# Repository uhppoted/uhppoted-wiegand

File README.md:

# uhppoted-wiegand

`uhppoted-wiegand` implements a RaspberryPi RP2040 based reader/emulator for a Wiegand-26 interface for:
- development, testing and debugging of access control software
- interfacing non-standard and off-brand readers and keypads to the UHPPOTE L0x access controllers

The project includes:
- _M5Stack_ Wiegand-26 emulator with:
   - isolated interface capable driving up to 32mA loads
   - can be powered from M5 bus, USB or external 12VDC supply
   - emulates both card reader and 4-bit/8-bit keypad modes
   - can operate either standalone or as an _M5Stack_ module

- breadboard prototypes
   - PIO based Wiegand-26 reader emulator which can write a Wiegand-26 card out to a controller
   - PIO based Wiegand-26 controller emulator which can read from Wiegand-26 reader and unlock a door
   - PIO based Wiegand-26 'universal' reader/writer implementation

## Status

### M5Stack

1. Wiegand emulator (Rev. 0)

|||

Includes:
- KiCad schematic and PCB layout
- Firmware for _Waveshare Tiny RP2040_
- Example Micropython application for _M5Stack_ _CoreS3_.

#### Errata
1. Pads for SK6812 are incorrectly numbered.
2. Anode and cathode swapped pads for D2, D3 and D4 are swapped.
3. ISO7841 doesn't allow RC filter on LED input.
4. Insufficient clearance around mounting holes.
5. DI and DO are pulled low on power-up (should default to _high_).
6. Solder mask does not include M5 connectors.
7. GPIO pins are incorrect (IO1 and IO2 instead of IO6 and IO7).

### Prototype

Breadboarded and Fritzing'ed implementations of:
- Wiegand-26 reader emulator
- Wiegand-26 controller emulator
- Wiegand-26 'universal' reader/writer

## Release Notes

### Current Release

## [0.9.1](https://codeberg.org/uhppoted/uhppoted-wiegand/releases/tag/v0.9.1) - 2026-10-13

1. Migrated from _github._ to _codeberg_.
2. Updated to Go 1.27.
3. Updated to pico-sdk_2.3.1.

## Breadboard

### Building from source

Required tools:
- [Raspberry Pi Pico C/C++ SDK](https://datasheets.raspberrypi.com/pico/raspberry-pi-pico-c-sdk.pdf)
- Compatible C/C++ compiler
- _make_
- [PicoProbe](https://github.com/raspberrypi/picoprobe) (optional but recommended)
- [OpenOCD](https://github.com/raspberrypi/openocd.git) (optional but recommended)
- [PicoTool](https://github.com/raspberrypi/picotool) (optional but recommended)

To build using the included _Makefile_:
```
git clone https://codeberg.org/uhppoted/uhppoted-wiegand.git
cd uhppoted-wiegand/breadboard/pico
make clean
make build
```

The `build` target produces both a UF2 and an ELF binary for installation on a _Raspberry Pi Pico_ using either:
- USB (using _BOOTSEL_)
- _PicoProbe_ + _OpenOCD_
- _PicoTool_

- The `make install` command installs the binary using _PicoTool_
- The `make run` command installs the binary using _PicoProbe_ and _OpenOCD_

### Usage

The provided software includes a **very** bare bones serial port command interface. Commands are (currently)
single letter mnemonics and need to be terminated by a carriage return and/or line feed.

The supported command set comprises:

| *Command*                | *Mode*       | *Description*                             |
| -------------------------|--------------|-------------------------------------------|
| TIME yyyy-mm-dd HH:mm:ss | _ALL_        | Set date/time                             |
| CARD nnnnnnnn            | _emulator_   | Emulates card swipe                       |
| CODE dddddd              | _emulator_   | Emulates keypad                           |
|                          |              |                                           |
| LIST ACL                 | _controller_ | List cards in ACL                         |
| CLEAR ACL                | _controller_ | Deletes all cards in ACL                  |
| GRANT nnnnnn dddddd      | _controller_ | Grant card (+ optional PIN) access rights |
| REVOKE nnnnnn            | _controller_ | Revoke card access rights                 |
| QUERY                    | _controller_ | Display last card read/write              |
|                          |              |                                           |
| MOUNT                    | _ALL_        | Mount SD card                             |
| UNMOUNT                  | _ALL_        | Unmount SD card                           |
| FORMAT                   | _ALL_        | Format SD card                            |
|                          |              |                                           |
| UNLOCK                   | _controller_ | Unlocks door for 5 seconds                |
|                          |              |                                           |
| OPEN                     | _emulator_   | Emulates door open contact                |
| CLOSE                    | _emulator_   | Emulates door close contact               |
| PRESS                    | _emulator_   | Emulates pushbutton press                 |
| RELEASE                  | _emulator_   | Emulates pushbutton release               |
|                          |              |                                           |
| BLINK                    | _ALL_        | Blinks reader LED 5 times                 |
| CLS                      | _ALL_        | Reinitialises terminal                    |
| REBOOT                   | _ALL_        | Reboot                                    |
| ?                        | _ALL_        | Display list of commands                  |

### Operating Modes

The codebase currently supports two operating modes:
- emulator
- controller

In _emulator_ mode the implementation writes a Wiegand-26 card code (or keypad PIN code) to an external Wiegand-26 interface
(e.g. a UHPPOTE controller). It also:
- emulates a door open/closed sensor
- emulates a door pushbutton
- detects the door locked/unlocked state

In _controller_ mode the implementation reads a Wiegand-26 card code (or keypad PIN code) from an external Wiegand-26 reader/keypad. It also:
- detects a door open/closed sensor state change
- detects a door pushbutton state change
- emulates a door lock/unlock
- implements card permissions and keypad passcodes

The operating mode is set by the combination of the code and the JUMPER_READ and JUMPER_WRITE inputs (set in _hwconfig.c_, 
GPIO7 and GPIO8 by default):
- the _controller_ binaries expect the JUMPER_READ input to be pulled LOW
- the _emulator_ binaries expected the JUMPER_WRITE input to be pulled LOW
- the _universal_ binaries start in _reader_ mode if the JUMPER_READ input is pulled LOW, or in _writer_ mode if the 
  JUMPER_WRITE is pulled LOW
- if both JUMPER_READ and JUMPER_WRITE are pulled LOW the operating mode is UNKNOWN.

### Keypad emulation

The code supports two keypad modes:
- 4-bit burst mode
- 8-bit burst mode

In 4 bit burst mode, each keypress is sent as 4 bit code followed by a 28-bit 'space', with keypad digits encoded as follows:

| Digit | 0    | 1    | 2    | 3    | 4    | 5    | 6    | 7    | 8    | 9    | *    | #    |
|-------|------|------|------|------|------|------|------|------|------|------|------|------|
| Code  | 0000 | 0001 | 0010 | 0011 | 0100 | 0101 | 0110 | 0111 | 1000 | 1001 | 1010 | 1011 |

In 8 bit burst mode, each keypress is sent as 8 bit code followed by a 24-bit 'space', with keypad digits encoded as follows:

| Digit | 0        | 1        | 2        | 3        | 4        | 5        | 6        | 7        | 8        | 9        | *        | #        |
|-------|----------|----------|----------|----------|----------|----------|----------|----------|----------|----------|----------|----------|
| Code  | 11110000 | 11100001 | 11010010 | 11000011 | 10110100 | 10100101 | 10010110 | 10000111 | 01111000 | 01101001 | 01011010 | 01001011 |

- In _emulator_ operating mode, the keypad mode is set by the `KEYPAD` build constant ('4-bit' or '8-bit')
- In _controller_ operating mode the keypad reader can detect and read both keypad encodings. A keycode is terminated by either a
  '#' or a 12.5 second timeout.

### Supervisor passcodes

The supervisor passcodes are _controller_ operating mode override codes that unconditionally unlocks the door.

The _controller_ operating mode supports up to four user-defined passcodes which can be set (or cleared) using the 
_PASSCODES_ command in the CLI. The passcodes may be up to 6 digits in length.

### Master passcode

In addition to the supervisor passcodes, the _controller_ operating mode provides for a MASTER override code that
unconditionally unlocks the door. The _MASTER_ override code is set at build time via the `MASTER_PASSCODE` build constant.

### Build constants

The _build constants_ in the _Makefiles_ define the initial operational settings:

| *Constant*           | *Description*                                                                                             |
|----------------------|-----------------------------------------------------------------------------------------------------------|
| `FACILITY_CODE`      | The default facility code for _emulator_ mode, used if the _CARD_ command card number is 5 digits or less |
| `SYSDATE`            | Initial system date                                                                                       |
| `SYSTIME`            | Initial system time                                                                                       |
| `MASTER_PASSCODE`    | Default master access override code                                                                       |
| `KEYPAD`             | Keypad mode ('4-bit' or '8-bit')                                                                          |
| `SSID`               | WiFi SSID                                                                                                 |
| `PASSWORD`           | WiFi password                                                                                             |
| `TCPD_CLI_PORT`      | TCP port for the Telnet CLI                                                                               |
| `TCPD_LOG_PORT`      | TCP port for the network logger                                                                           |
| `TCPD_SERVER_IDLE`   | Idle time (seconds) after which the TCP server closes all connections and restarts                        |
| `TCPD_CLIENT_IDLE`   | Idle time (seconds) after which a Telnet CLI client connection is closed                                  |
| `TCPD_POLL_INTERVAL` | Internal TCP handler poll interval (ms)                                                                   |
## License

Hardware is licensed under the CERN-OHL-S-2.0-S license, software is licensed under the MIT license.

## References and Related Projects

1. [Getting started with the Raspberry Pi Pico](https://datasheets.raspberrypi.com/pico/getting-started-with-pico.pdf)

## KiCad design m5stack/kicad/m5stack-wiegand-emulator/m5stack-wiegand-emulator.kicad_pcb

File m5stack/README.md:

# M5Stack Wiegand Emulator

RP2040 _M5Stack_ module to emulate a Wiegand reader:

- Emulates a single Wiegand-26 card reader/keypad with an LED. 
- Implements the M5Stack serial interface.
- Intended for use with an M5 _base_ module but can optionally be powered via the external connector
  for standalone use.

## Raison d'être

Mostly to avoid having to dig out a breadboard and figure how it worked all over again every time I needed
to test a Wiegand interface.

## Notes

1. The emulator uses a line driver to interface to the external controller i.e. it is not an open-collector
   and cannot be "parallelised" (as in e.g. [Will this circuit for two Wiegand card readers allow them to talk to one control board?](https://electronics.stackexchange.com/questions/535159/will-this-circuit-for-two-wiegand-card-readers-allow-them-to-talk-to-one-control). Which TBH is kindof a weird thing to do but ..).

## Status

**IN DEVELOPMENT**

## Design Notes

### Rev.0

1. The RP2040 is **way** overkill for this application but makes for a nice development setup.
2. It's more logicial to have the ISO784x on the other side of the RP2040 but for now it allows for powering via
   USB during development.

#### Errata
1. Pads for WS2812/SK6812 are incorrectly numbered.
2. Pads for D2, D3 and D4 are incorrect (anode and cathode swapped).
3. ISO7841 doesn't allow RC filter on LED input.

## References

1. [M5Stack](https://m5stack.com)
2. [WaveShare RP2040-Tiny](https://www.waveshare.com/wiki/RP2040-Tiny)
3. [M5 Core Schematic(20171206)](https://m5stack.oss-cn-shenzhen.aliyuncs.com/resource/docs/schematic/Core/M5-Core-Schematic(20171206).pdf)

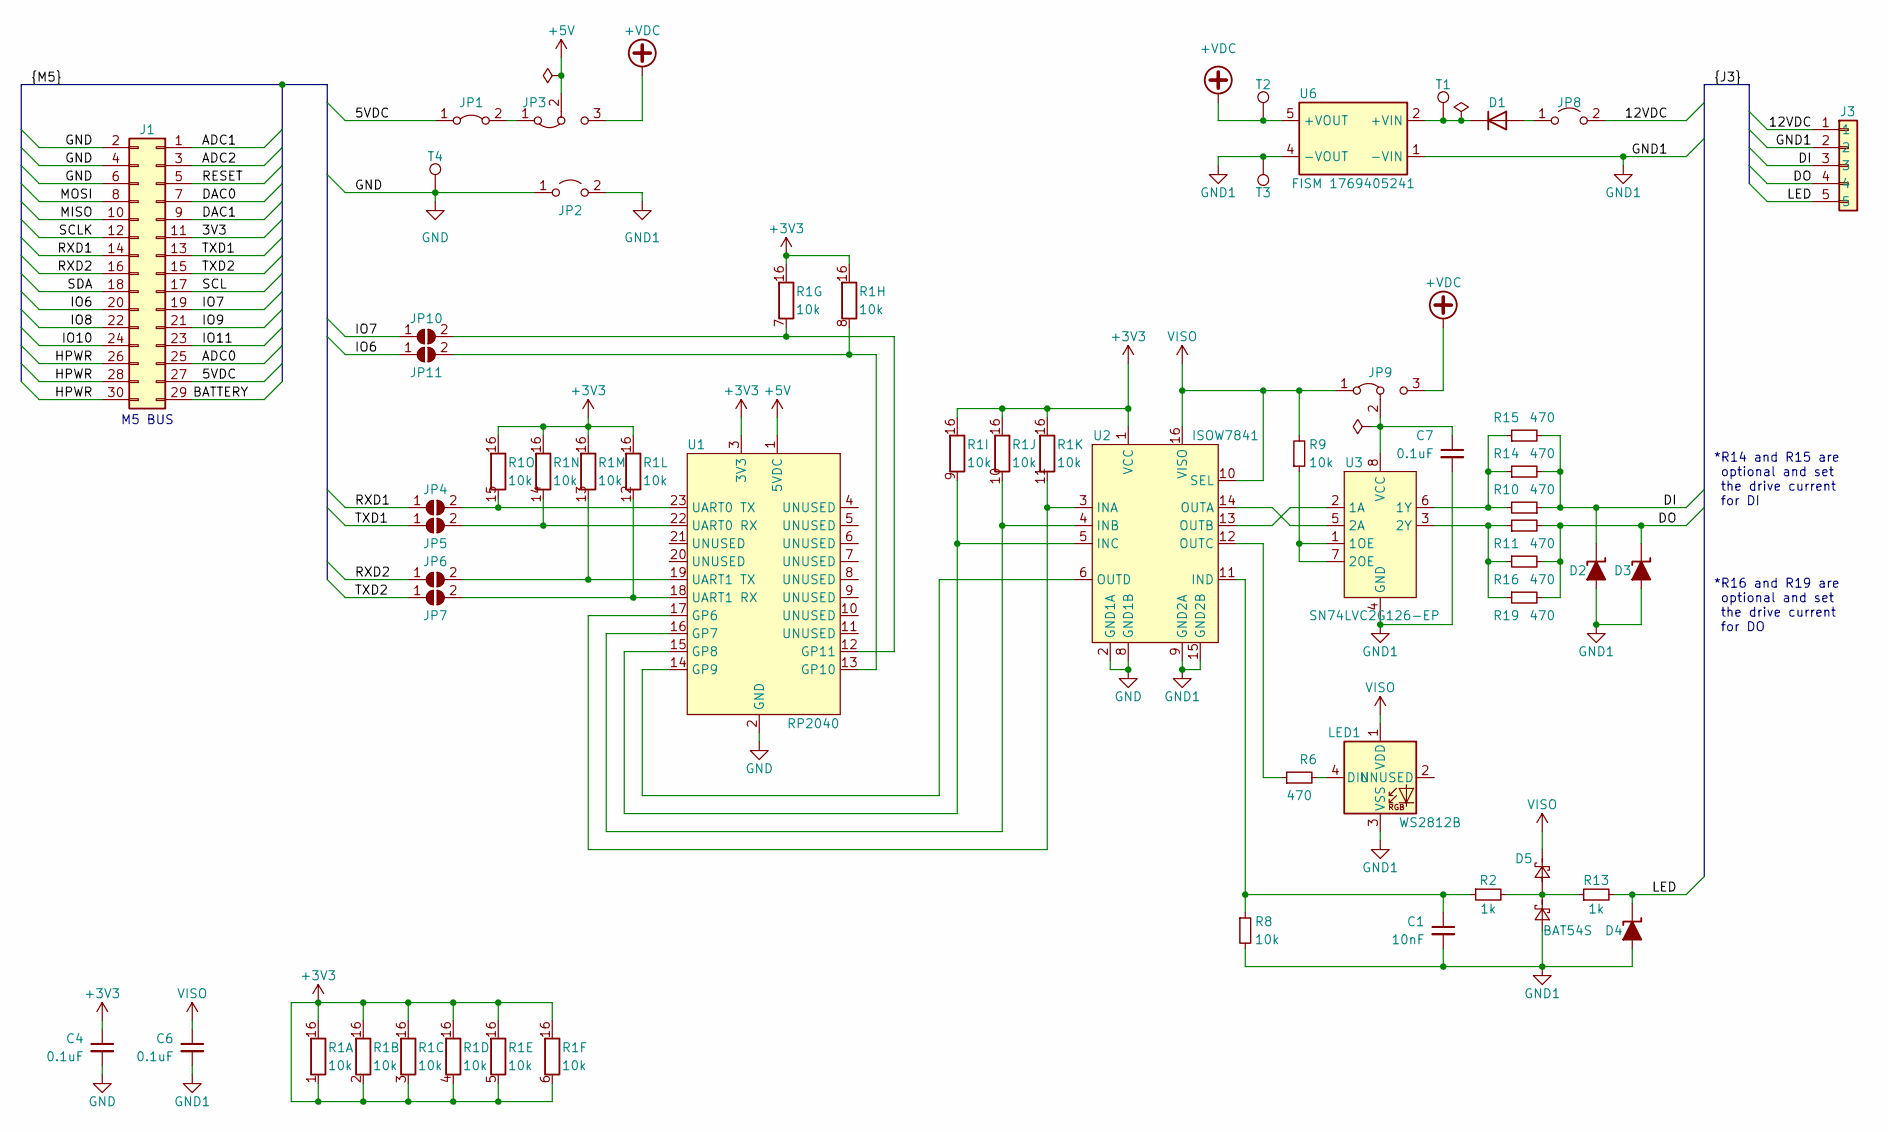
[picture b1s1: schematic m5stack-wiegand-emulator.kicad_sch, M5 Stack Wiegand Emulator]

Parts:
C1: 10nF; C_0805_2012Metric_Pad1.18x1.45mm_HandSolder
C4, C6, C7: 0.1uF; C_0805_2012Metric_Pad1.18x1.45mm_HandSolder
D1: GF1A; DIODE_DO-214BA
D2, D3, D4: MSP5.0A
D5: BAT54S; SOT-23
J1: 2x15 socket header; M5Stack Bus SMD connector
J3: 1x5 female; Molex 532610571
JP1, JP2: Jumper_2_Bridged; PinHeader_1x02_P1.27mm_Vertical
JP3, JP9: Jumper_3_Bridged12; PinHeader_1x03_P1.27mm_Vertical
JP4, JP5, JP6, JP7, JP10, JP11: Jumper:SolderJumper_2_Open; SolderJumper-2_P1.3mm_Open_RoundedPad1.0x1.5mm
JP8: Jumper; PinHeader_1x02_P1.27mm_Vertical
LED1: WS2812B; LED_WS2812B_PLCC4_5.0x5.0mm_P3.2mm
R1: 10k; EXB-Q16P103J
R2, R13: 1k; R_0805_2012Metric_Pad1.20x1.40mm_HandSolder
R6, R10, R11, R14, R15, R16, R19: 470; R_0805_2012Metric_Pad1.20x1.40mm_HandSolder
R8, R9: 10k; R_0805_2012Metric_Pad1.20x1.40mm_HandSolder
T1, T2, T3, T4: TestPoint; TestPoint_THTPad_1.0x1.0mm_Drill0.5mm
U1: RP2040; RP2040-TINY
U2: ISOW7841; DWE0016A
U3: SN74LVC2G126-EP; VSSOP-8_2.4x2.1mm_P0.5mm
U6: FISM 1769405241; WPME-FISM_SMT-8_1769205241

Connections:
+3V3: C4.1, R1.1 (R15.2), R1.2 (R2.2), R1.3 (R3.2), R1.4 (R4.2), R1.5 (R5.2), R1.6 (R6.2), R1.16 (R1), U1.3 (3V3), U2.1 (VCC)
+5V: JP3.2 (C), U1.1 (5VDC)
+VDC: JP3.3 (B), JP9.3 (B), T2.1, U6.5 (+VOUT)
/3V3: J1.11
/5VDC: J1.27, JP1.1 (A)
/12VDC: J3.1, JP8.2 (B)
/ADC0: J1.25
/ADC1: J1.1
/ADC2: J1.3
/BATTERY: J1.29
/DAC0: J1.7
/DAC1: J1.9
/DI: D2.1 (A1), J3.3, R10.1, R14.2, R15.2
/DO: D3.1 (A1), J3.4, R11.2, R16.2, R19.2
/HPWR: J1.26, J1.28, J1.30
/IO6: J1.20, JP11.1 (A)
/IO7: J1.19, JP10.1 (A)
/IO8: J1.22
/IO9: J1.21
/IO10: J1.24
/IO11: J1.23
/LED: D4.1 (A1), J3.5, R13.2
/MISO: J1.10
/MOSI: J1.8
/RESET: J1.5
/RXD1: J1.14, JP4.1 (A)
/RXD2: J1.16, JP6.1 (A)
/SCL: J1.17
/SCLK: J1.12
/SDA: J1.18
/TXD1: J1.13, JP5.1 (A)
/TXD2: J1.15, JP7.1 (A)
GND: C4.2, J1.2, J1.4, J1.6, JP2.1 (A), T4.1, U1.2 (GND), U2.2 (GND1A), U2.8 (GND1B)
GND1: C1.2, C6.2, C7.2, D2.2 (A2), D3.2 (A2), D4.2 (A2), D5.1 (A), J3.2, JP2.2 (B), LED1.3 (VSS), R8.2, T3.1, U2.9 (GND2A), U2.15 (GND2B), U3.4 (GND), U6.1 (-VIN), U6.4 (-VOUT)
unnamed: D1.2 (A), JP8.1 (A)
unnamed: D1.1 (K), T1.1, U6.2 (+VIN)
unnamed: D5.3 (COM), R2.2, R13.1
unnamed: JP1.2 (B), JP3.1 (A)
unnamed: JP4.2 (B), R1.15 (R15.2), U1.23 (UART0 TX)
unnamed: JP5.2 (B), R1.14 (R15.2), U1.22 (UART0 RX)
unnamed: JP6.2 (B), R1.13 (R15.2), U1.19 (UART1 TX)
unnamed: JP7.2 (B), R1.12 (R15.2), U1.18 (UART1 RX)
unnamed: C7.1, JP9.2 (C), U3.8 (VCC)
unnamed: JP10.2 (B), R1.7 (R7.2), U1.12 (GP11)
unnamed: JP11.2 (B), R1.8 (R8.2), U1.13 (GP10)
unnamed: LED1.4 (DIN), R6.2
unnamed: R1.9 (R15.2), U1.15 (GP8), U2.5 (INC)
unnamed: R1.10 (R15.2), U1.16 (GP7), U2.4 (INB)
unnamed: R1.11 (R15.2), U1.17 (GP6), U2.3 (INA)
unnamed: U1.14 (GP9), U2.6 (OUTD)
unnamed: C1.1, R2.1, R8.1, U2.11 (IND)
unnamed: U2.14 (OUTA), U3.5 (2A)
unnamed: U2.13 (OUTB), U3.2 (1A)
unnamed: R6.1, U2.12 (OUTC)
unnamed: R9.1, U3.1 (1OE), U3.7 (2OE)
unnamed: R10.2, R14.1, R15.1, U3.6 (1Y)
unnamed: R11.1, R16.1, R19.1, U3.3 (2Y)
VISO: C6.1, D5.2 (K), JP9.1 (A), LED1.1 (VDD), R9.2, U2.10 (SEL), U2.16 (VISO)

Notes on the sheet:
*R14 and R15 are optional and set the drive current for DI
*R16 and R19 are optional and set the drive current for DO
M5 BUS

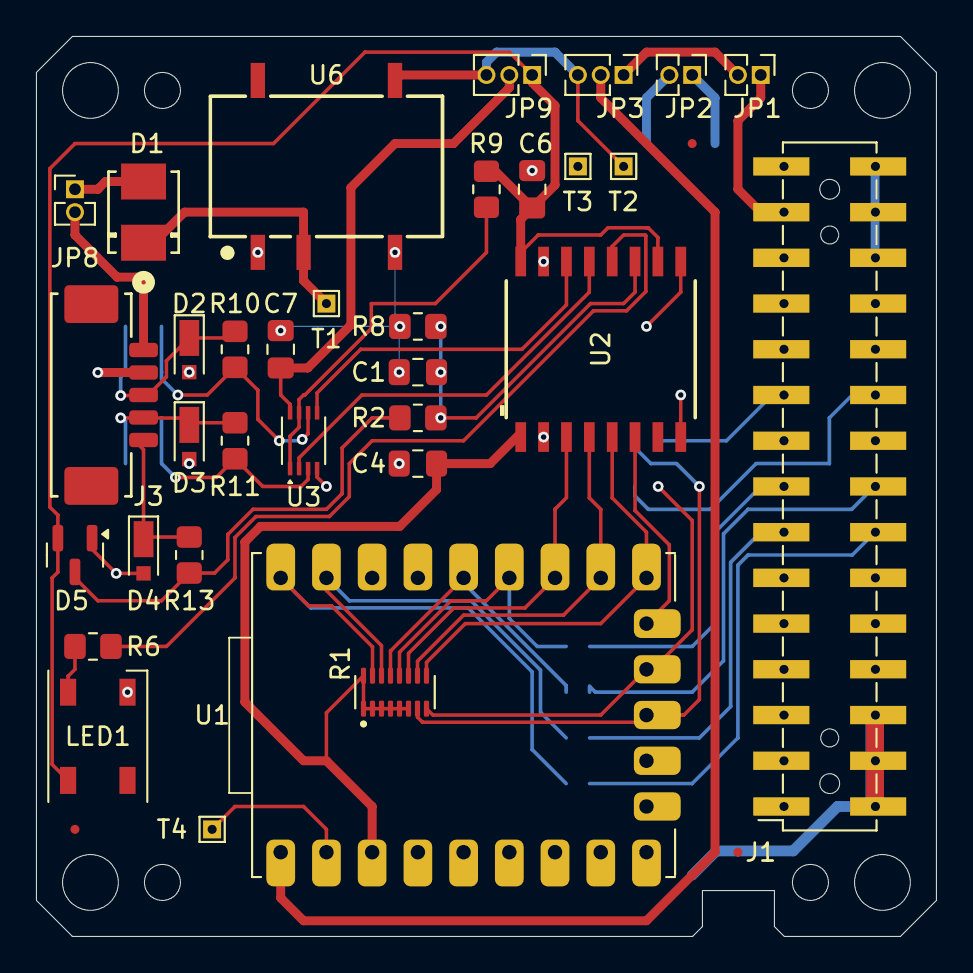
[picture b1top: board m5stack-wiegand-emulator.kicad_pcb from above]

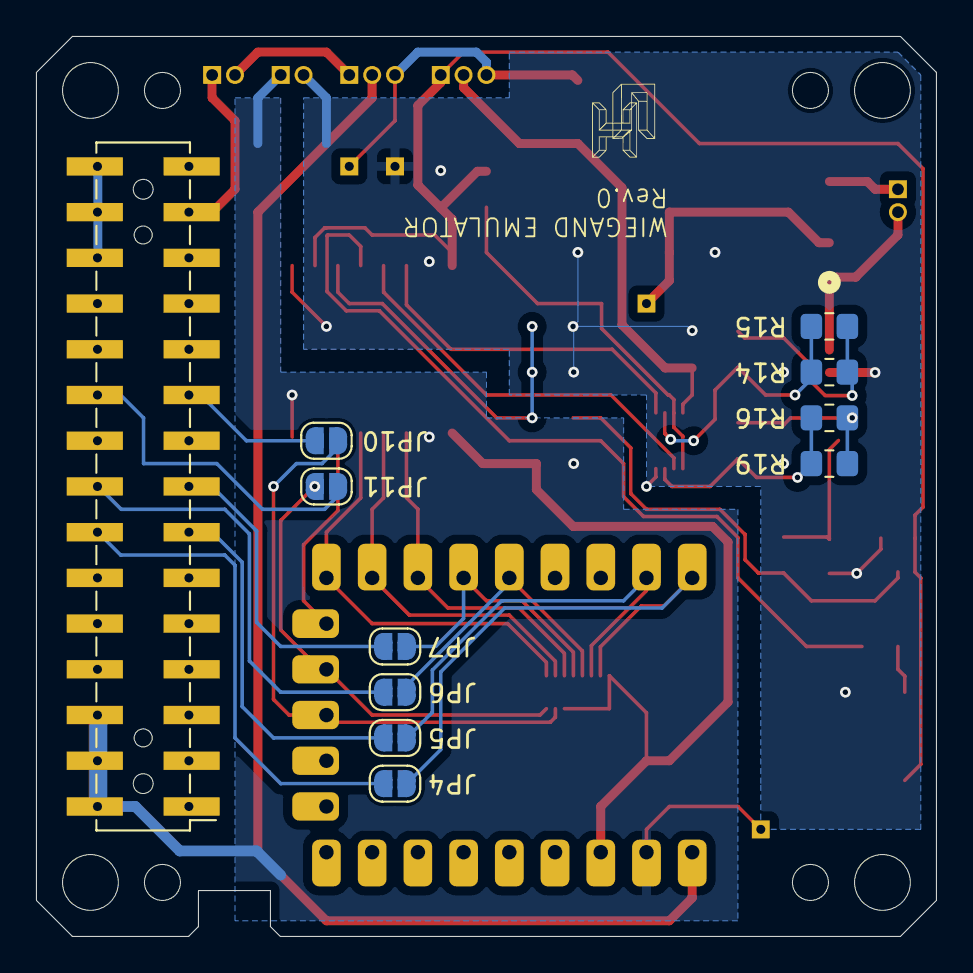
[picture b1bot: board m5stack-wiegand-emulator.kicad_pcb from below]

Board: 2 copper layers, 50.0 x 50.0 mm, 54 parts (10 on the bottom side), 41 nets.

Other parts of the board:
F1, F2, F3: Fiducial_0.5mm_Mask1mm
M1, M2, M3, M4: M5Stack 3.1mm mounting hole
M5, M6, M7, M7#2: M5Stack 2mm mounting hole

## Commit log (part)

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2022-12-02 CLI: queried the terminal window size on start to set the scrolling area
2022-12-03 CLI: backspace
2022-12-06 Cleared CLI command buffer after idle for 10s
2022-12-06 Fixed static CLI buffer initialisation
2022-12-08 (interim commit) writer skeleton
2022-12-10 emulator: shifted bits out to D0/D1
2022-12-11 Card write + readback
2022-12-11 Replaced WRITE delay kluge with tweaked clock
2022-12-20 Fixed CLI card/facility-code parsing
2022-12-21 Ignore 'write' command if not in emulator mode
2022-12-21 Cleaned up breadboard
2022-12-22 Initial PIO LED handler
2022-12-27 Hooked up emulator LED input to green LED
2022-12-27 Reworked emulator LED PIO to use 'pin' rather than 'gpio'
2022-12-28 Reader LED blink on granted/denied
2022-12-29 Moved reader LED blink delay to an alarm handler
2022-12-30 Added 'grant' and 'revoke' commands to the CLI
2022-12-30 Moved 'mode' inputs to GPIO 6 and 7 to free up UART1 and I2C ports
2023-01-02 Added overarching read timeout in case timeout alarm isn't set
2023-01-05 Implemented startup delay
2023-01-05 Split VT100 'clear screen' and 'set scroll area' invocations to mitigate CLI startup weirdness
2023-01-06 CLI: 'help' command
2023-01-09 Initial buzzer skeleton
2023-01-11 (interim commit) hunting down emulator freeze bug
2023-01-12 Redefined last.granted as enum
2023-01-13 'beep' on card write
2023-01-13 Renamed READER to CONTROLLER
2023-01-16 fritzing: initial import
2023-01-19 fritzing: added SD card breakout
2023-01-20 fritzing: adding SD card breakout board
2023-01-24 Reorganised green and orange LEDs to match Fritzing
2023-01-25 Writing to SD card
2023-01-26 Shuffled LEDs
2023-01-27 Initialising ACL from SD card
2023-01-27 Updated Fritzing layout for swapped buzzer and red LED pin
2023-01-30 Updated ACL on SD card on grant/revoke
2023-02-01 Updated breadboard with Phoenix connectors
2023-02-02 Fritzing: fixed Wiegand D0/D1 routing
2023-02-03 Cleaned up FatFS lib
2023-02-03 Added relay inputs to Fritzing
2023-02-06 Added pull-up and protection resistors to relay inputs
2023-02-07 (interim commit) basic relay monitor
2023-02-08 Added LPF to relay states
2023-02-09 Adding relay module to Fritzing
2023-02-13 Routing relays for pushbutton and door contact
2023-02-15 Fritzing: reworking layout for TPIC6592 I/O expander
2023-02-16 fritzing: shuffling v1 breadboard layout
2023-02-17 Routed Fritzing v.1 schematic
2023-02-21 Fritzing: corrected TPIC6B595 connections
2023-02-22 Replaced relay module with DPDT driven by TPIC6B595
2023-02-24 v1 breadboard: revised Wiegand reader/writer pin assignment
2023-02-27 Updated buzzer pin assignment for v1 breadboard
2023-02-27 (interim commit) reassigned LED GPIO pins to TPIC SPI
2023-03-01 Moving LEDs to TPIC6B595
2023-03-02 Re-enabled reader/writer LED
2023-03-03 Door open/close relay
2023-03-03 Door contact monitor
2023-03-06 Added basic pushbutton read/write
2023-03-07 Wrapped up reed relay contact emulation
2023-03-08 wiegand-emulator: initial import
2023-03-08 wiegand-emulator: removed door unlock
2023-03-08 wiegand-emulator: removed SD card
2023-03-09 wiegand-controller: initial import
2023-03-09 wiegand-controller: CONTROLLER mode flag
2023-03-09 Moved access grant/deny to wiegand.c and controller.c
2023-03-10 Added derivative Fritzing layouts for emulator and controller
2023-03-10 fritzing: fixed mode jumper for controller
2023-03-13 Split CLI into UART and command handler
2023-03-14 Commonalised system stuff
2023-03-15 Initial import for USB CLI
2023-03-16 Added USB variants for controller/emulator
2023-03-16 Commonalised UART/USB CLIs
2023-03-17 Preparing for v0.8.4 release
2023-05-01 PicoW initial wireless skeleton (cf. https://github.com/uhppoted/uhppoted-wiegand/issues/1)
2023-05-02 Externalised TPIC state to a struct and added check for initialised (blocking call)
2023-05-02 Externalised LEDs state to a struct and added check for initialised (blocks if not initialised)
2023-05-03 TCPd skeleton tx/rx
2023-05-04 Replaced blocking connect with async/poll and reenabled watchdog.
2023-05-05 picow: cleaned up link management logic
2023-05-08 Preparing to branch to restructure the PIOs
2023-05-08 Shuffled PIOs and SMs to make space for CYW43 driver
2023-05-10 Replaced LED in PIO with a timer interrupt to free up PIO1 for the PicoW
2023-05-11 Seperated LED poll and output timer initialisation
2023-05-11 Moved WiFi support to base and added PicoW variant to controller
2023-05-11 Added picow variant to reference implementation
2023-05-12 PicoW: closed idle connections
2023-05-12 picow: handled remote connection close
2023-05-15 tcpd: implemented per connection state to support multiple client connections
2023-05-15 tcpd: removed no longer used tcpd_result
2023-05-17 tcpd: shutdown server on idle
2023-05-19 Verified TCP send buffering works and reduced buffer sizes
2023-05-19 PicoW: logd skeleton and TCP listener
2023-05-23 Routed logd messages to tcpd
2023-05-25 PicoW: formatted CLI responses (slightly) to differentiate them in the terminal
2023-05-25 Added cyw43_arch_lwip_begin/end around critical sections
2023-05-26 Added TCP ports, poll interval and idle timeouts to the CMakeList variables
2023-05-29 Workaround for SD card detect interrupt conflict with cyw43 and USB enabled builds
2023-05-30 Renamed controller/picow to controller/wifi
2023-05-31 NTS: weird wifi disconnect resolved - cable modem instability
2023-05-31 reference:usb+wifi variant
2023-06-01 (debugging SD card detect+USB+WiFi interrupt conflict)
2023-06-02 Restructured to seperate pico and picow variants
2023-06-06 Added base variant to reference/picow
2023-06-06 controller-picow-base: deferred SYSLED off to a queued msg to avoid lockup
2023-06-07 cyw43: commonalised initialisation in core/picow/cwy43.c
2023-06-07 controller: PicoW base variant
2023-06-07 Updated emulator-wifi to use PicoW sysled
2023-06-07 Cleaning up variant builds
2023-06-08 Initialised CYW43 SYSLED immediately after cyw43_arch_init (workaround for lock-acquire hang)
2023-06-12 Fixed logging in the base Pico versions
2023-06-12 Cleaned up TODO list for release v0.8.5
2023-06-12 Updated CHANGELOG and README for release v0.8.5
2023-08-14 Moved SD card read to ACL, preparatory to using onboard flash (cf. https://github.com/uhppoted/uhppoted-wiegand/issues/2)
2023-08-15 ACL: flash read/write (partial)
2023-08-16 flash: validated header magic word, version and card count on read
2023-08-17 flash: validated ACL CRC
2023-08-18 Reworked acl_load/save function signatures to return result code rather than message
2023-08-18 flash: bump ACL version on write
2023-08-21 flash: extracted get-current-page
2023-08-21 Reinstated ACL SD card read/write
2023-08-21 Cleaned up ACL logic a bit
2023-08-23 github workflow: initial skeleton
2023-08-23 github workflow: checkout project
2023-08-23 github workflow: relocating pico-sdk
2023-08-23 github workflow: build-all
2023-08-23 github workflow: set SDK path
2023-08-23 github workflow: rework credentials as Makefile variable
2023-08-28 Preparing release v0.8.6
2023-09-12 Added keypad emulation command to CLI
2023-09-14 Initialised 'door closed' relay on startup
2023-09-15 Simplifed card read logic down to a single 10ms timeout
2023-09-15 Reading 4-bit Wiegand keypad codes (cf. https://github.com/uhppoted/uhppoted-wiegand/issues/4)
2023-09-20 Updated all emulator variants for keycodes (cf. https://github.com/uhppoted/uhppoted-wiegand/issues/4)
2023-09-22 Adding keycode support to controllers (cf. https://github.com/uhppoted/uhppoted-wiegand/issues/4)
2023-09-26 Moved set-time CLI command implementation to core
2023-09-27 Added 'passcodes' CLI command to set override passcodes
2023-09-28 Persisted passcodes to onboard flash (cf. https://github.com/uhppoted/uhppoted-wiegand/issues/4)
2023-10-02 Included passcodes in flash CRC (cf. https://github.com/uhppoted/uhppoted-wiegand/issues/4)
2023-10-04 Fixed write ACL to SD card logic
2023-10-05 Tidied up SD card and flash ACL read/write
2023-10-09 8-bit burst mode keycode read/write (cf. https://github.com/uhppoted/uhppoted-wiegand/issues/4)
2023-10-10 (interim commit) skeleton implementation of card+keycode
2023-10-11 card+PIN write emulation
2023-10-13 Added optional PIN code to CLI 'grant'
2023-10-17 controller: moved 'revoke' command to core CLI
2023-10-17 controller: card PIN timeout
2023-10-18 Added facility code and card number validation to acl::grant
2023-10-19 Renamed 'reference' to 'universal'
2023-10-19 Updated universal/picow/base for card + PIN (cf. https://github.com/uhppoted/uhppoted-wiegand/issues/4)
2023-10-23 Fixed the SD card read/write logic for card+PIN (cf. https://github.com/uhppoted/uhppoted-wiegand/issues/4)
2023-10-25 Replaced READER/WRITER with CONTROLLER/EMULATOR throughout and added keypad emulation information to README (cf. https://github.com/uhppoted/uhppoted-wiegand/issues/4)
2023-10-25 Fixed typo in README
2023-12-01 Release v0.8.7
2024-03-23 Bumped version of github workflow actions
2024-03-26 Preparing release v0.8.8
2024-07-13 Fixed double keycode processing in emulator/picow
2024-08-06 Testing 8-bit keypad code
2024-09-06 Modified github workflow to use Pico SDK v1.1.5 (master branch broken)
2024-09-06 Modified github workflow to use Pico SDK 1.1.5 (master branch seems broken)
2024-09-06 Testing Pico SDK 2.0.0 on github
2024-09-09 Relabelled 'rx' in READ.pio - conflicts with RP2350 reserved word (cf. https://github.com/uhppoted/uhppoted-wiegand/issues/6)
2025-01-30 Bumped version for next development cycle
2025-02-03 M5 stack: initial setup
2025-02-03 Updating github workflow for restructured folders
2025-02-03 Fixed typo in Makefile
2025-02-03 Removed debugging from github workflow
2025-02-04 M5: added opto-isolators
2025-02-05 M5: reworked RP2040-Tiny symbol
2025-02-05 M5: reworking WS2812 to use SN74HCT245
2025-02-06 M5Stack: reworked WS2821 to use SN74HCT1G125
2025-02-10 M5: pullup for WS2812 DIN
2025-02-10 M5: basic LTSpice simulation for line driver
2025-02-11 M5: reworked to use ISO7841 and INC to drive line driver OE
2025-02-13 M5: replaced TPS62713 regulator with TPS629206 (SOT-583)
2025-02-14 M5: replaced MOVs with TVS diodes
2025-02-18 M5: added BAT54S input protection to LED
2025-02-18 M5: corrected cutout offset on PCB
2025-02-19 M5: adding missing footprints
2025-02-20 M5: changed L1 footprint to Vishay/1210
2025-02-21 M5: placed all footprints
2025-02-24 M5: replaced discrete'ish switchmode with module
2025-02-25 M5: added solder jumpers for TC/RX
2025-02-25 M5: replaced WS2812 driver with output from ISOW7843
2025-02-26 M5: reworked PCB footprints for overlap
2025-03-03 M5: routing PCB
2025-03-04 Relocated J3 connector and rerouted
2025-03-05 M5: routed DI/DO signals
2025-03-06 M5: routing LED IN signal
2025-03-10 Updated license to CERN-OHL-S-2 for the hardware
2025-03-11 M5: recalculated LED input resistance
2025-03-12 M5: PCB routed and DRC'd
2025-03-17 M5: replaced J1+J2 with single THT connector
2025-03-18 M5: cleaned up tracks and vias
2025-03-18 M5: flipped (rip up)
2025-03-19 M5: schematic tidy-up
2025-03-20 M5: reworked M5 bus connector footprint
2025-03-24 M5: added optional GPIO connections
2025-04-16 M5: removed solder jumpers and test points from BOM
2025-06-18 M5: routed all prints to sys::print queue
2025-06-19 M5: basic CLI
2025-06-25 M5: renamed LED to SK6812
2025-06-26 M5: LED 25Hz LPF
2025-06-26 M5: added ISOW7841 RC filter to Rev.0 errata list
2025-06-30 M5: Wiegand write skeleton implementation
2025-07-02 M5: preconfigured PIO and SM assignments
2025-07-02 M5: blink SK6812
2025-07-07 M5: added 'set keypad mode' command
2025-07-08 M5: GPIO interface
2025-07-09 (experimental) tinyusb
2025-07-09 USB: added tinyusb RX handler
2025-07-09 Splitting USB and UART implementations
2025-07-15 CoreS3: working GPIO example
2025-07-17 CoreS3: uart2 'CARD' command
2025-07-17 CoreS3: keypad code
2025-07-21 M5: returned ok/error on UART command
2025-07-22 M5: renamed tiny-uart to tiny-coreS3
2025-07-23 M5: USB command protocol
2025-07-24 M5: commonalized API swipe/keycode implementation
2025-07-24 M5: fixing README images
2025-07-24 Fixing README images
2025-07-29 M5: checked out EXT power
2025-10-01 M5: added keypad to demo application
2025-11-21 Added notes for M5 Stack
